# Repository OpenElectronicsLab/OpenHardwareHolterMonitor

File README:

OpenHardwareHolterMonitor is still in early development

This is not a medical device; it is not intended for diagnosis or treatment
of any medical condition.

http://openelectronicslab.github.io/OpenHardwareHolterMonitor/

LICENSE

Software and firmware is licensed under the GPL version 3 as published by the Free Software Foundataion or (at your option) any later version.

https://www.gnu.org/licenses/gpl-3.0.txt

Hardware designs and documentation are licnesed under the CERN Open Hardware
License version 1.1 or (at your option) any later version.

https://www.ohwr.org/licenses/cern-ohl/license_versions/v1.1

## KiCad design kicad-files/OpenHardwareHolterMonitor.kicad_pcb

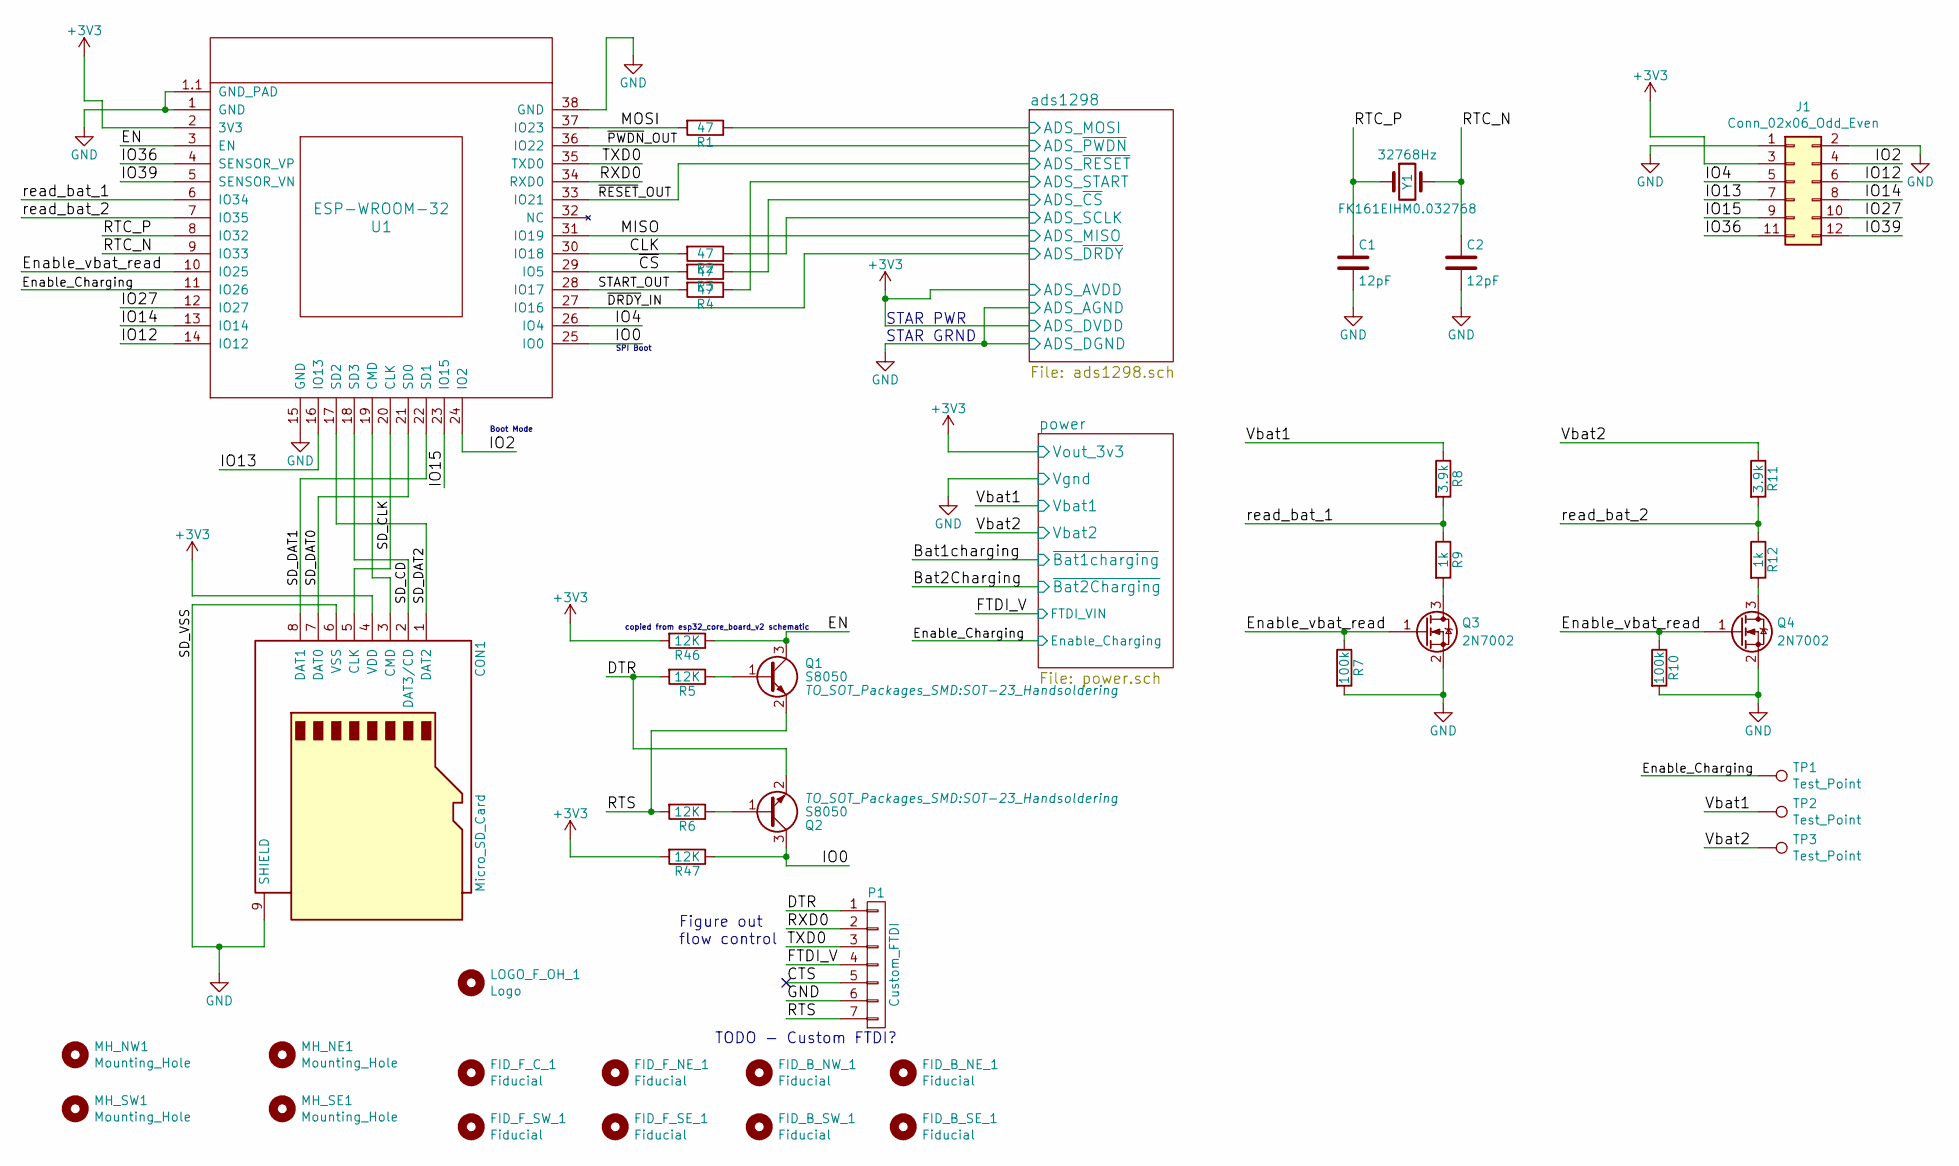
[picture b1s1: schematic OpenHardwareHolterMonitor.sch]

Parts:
C1, C2: 12pF; C_0603_HandSoldering
CON1: Micro_SD_Card; MicroSd_Wurth_693072010801
FID_B_NE_1: Fiducial; Fiducial_1mm_Dia_2.54mm_Outer_CopperTop
FID_B_NW_1: Fiducial; Fiducial_1mm_Dia_2.54mm_Outer_CopperTop
FID_B_SE_1: Fiducial; Fiducial_1mm_Dia_2.54mm_Outer_CopperTop
FID_B_SW_1: Fiducial; Fiducial_1mm_Dia_2.54mm_Outer_CopperTop
FID_F_C_1: Fiducial; Fiducial_1mm_Dia_2.54mm_Outer_CopperTop
FID_F_NE_1: Fiducial; Fiducial_1mm_Dia_2.54mm_Outer_CopperTop
FID_F_SE_1: Fiducial; Fiducial_1mm_Dia_2.54mm_Outer_CopperTop
FID_F_SW_1: Fiducial; Fiducial_1mm_Dia_2.54mm_Outer_CopperTop
J1: Conn_02x06_Odd_Even; Pin_Header_Straight_2x06_Pitch1.27mm
LOGO_F_OH_1: Logo; OSHW-Logo2_9.8x8mm_SilkScreen
MH_NE1: Mounting_Hole; MountingHole_2.2mm_M2_ISO7380
MH_NW1: Mounting_Hole; MountingHole_2.2mm_M2_ISO7380
MH_SE1: Mounting_Hole; MountingHole_2.2mm_M2_ISO7380
MH_SW1: Mounting_Hole; MountingHole_2.2mm_M2_ISO7380
P1: Custom_FTDI; Pin_Header_Straight_1x07_Pitch2.54mm
Q1, Q2: S8050; SOT-23_Handsoldering
Q3, Q4: 2N7002; SOT-23_Handsoldering
R1, R2, R3, R4: 47; R_0603_1608Metric_Pad1.05x0.95mm_HandSolder
R5, R6, R46, R47: 12K; R_0603_1608Metric_Pad1.05x0.95mm_HandSolder
R7, R10: 100k; R_0603_1608Metric_Pad1.05x0.95mm_HandSolder
R8, R11: 3.9k; R_0603_1608Metric_Pad1.05x0.95mm_HandSolder
R9, R12: 1k; R_0603_1608Metric_Pad1.05x0.95mm_HandSolder
TP1, TP2, TP3: Test_Point; Measurement_Point_Square-SMD-Pad_Small
U1: ESP-WROOM-32; MODULE_ESP-WROOM-32
Y1: 32768Hz; K161

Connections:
+3V3: CON1.4 (VDD), J1.3, R46.2, R47.2, U1.2 (3V3); also elsewhere on the board
/CLK: R2.2, U1.30 (IO18)
/CTS: P1.5
/DTR: P1.1, Q2.2 (E), R5.2
/EN: Q1.3 (C), R46.1, U1.3 (EN)
/Enable_Charging: TP1.1, U1.11 (IO26); also elsewhere on the board
/Enable_vbat_read: Q3.1 (G), Q4.1 (G), R7.1, R10.1, U1.10 (IO25)
/FTDI_V: P1.4; also elsewhere on the board
/IO0: Q2.3 (C), R47.1, U1.25 (IO0)
/IO2: J1.4, U1.24 (IO2)
/IO4: J1.5, U1.26 (IO4)
/IO12: J1.6, U1.14 (IO12)
/IO13: J1.7, U1.16 (IO13)
/IO14: J1.8, U1.13 (IO14)
/IO15: J1.9, U1.23 (IO15)
/IO27: J1.10, U1.12 (IO27)
/IO36: J1.11, U1.4 (SENSOR_VP)
/IO39: J1.12, U1.5 (SENSOR_VN)
/MISO: U1.31 (IO19); also elsewhere on the board
/MOSI: R1.2, U1.37 (IO23)
/RTC_N: C2.1, U1.9 (IO33), Y1.2
/RTC_P: C1.1, U1.8 (IO32), Y1.1
/RTS: P1.7, Q1.2 (E), R6.2
/RXD0: P1.2, U1.34 (RXD0)
/SD_CD: CON1.2 (DAT3/CD), U1.18 (SD3)
/SD_CLK: CON1.5 (CLK), U1.20 (CLK)
/SD_DAT0: CON1.7 (DAT0), U1.21 (SD0)
/SD_DAT1: CON1.8 (DAT1), U1.22 (SD1)
/SD_DAT2: CON1.1 (DAT2), U1.17 (SD2)
/START_OUT: R4.2, U1.28 (IO17)
/TXD0: P1.3, U1.35 (TXD0)
/Vbat1: R8.1, TP2.1; also elsewhere on the board
/Vbat2: R11.1, TP3.1; also elsewhere on the board
/ads1298/ADS_MOSI: R1.1; also elsewhere on the board
/ads1298/ADS_SCLK: R2.1; also elsewhere on the board
/ads1298/ADS_START: R4.1; also elsewhere on the board
/ads1298/ADS_~CS~: R3.1; also elsewhere on the board
/read_bat_1: R8.2, R9.1, U1.6 (IO34)
/read_bat_2: R11.2, R12.1, U1.7 (IO35)
/~CS~: R3.2, U1.29 (IO5)
/~DRDY~_IN: U1.27 (IO16); also elsewhere on the board
/~PWDN~_OUT: U1.36 (IO22); also elsewhere on the board
/~RESET~_OUT: U1.33 (IO21); also elsewhere on the board
GND: C1.2, C2.2, CON1.6 (VSS), CON1.9 (SHIELD), J1.1, J1.2, P1.6, Q3.2 (S), Q4.2 (S), R7.2, R10.2, U1.1 (GND), U1.1.1 (GND_PAD), U1.15 (GND), U1.38 (GND); also elsewhere on the board
unnamed: CON1.3 (CMD), U1.19 (CMD)
unnamed: Q1.1 (B), R5.1
unnamed: Q2.1 (B), R6.1
unnamed: Q3.3 (D), R9.2
unnamed: Q4.3 (D), R12.2

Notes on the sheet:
copied from esp32_core_board_v2 schematic
Figure out flow control
Boot Mode
SPI Boot
STAR PWR STAR GRND
TODO - Custom FTDI?

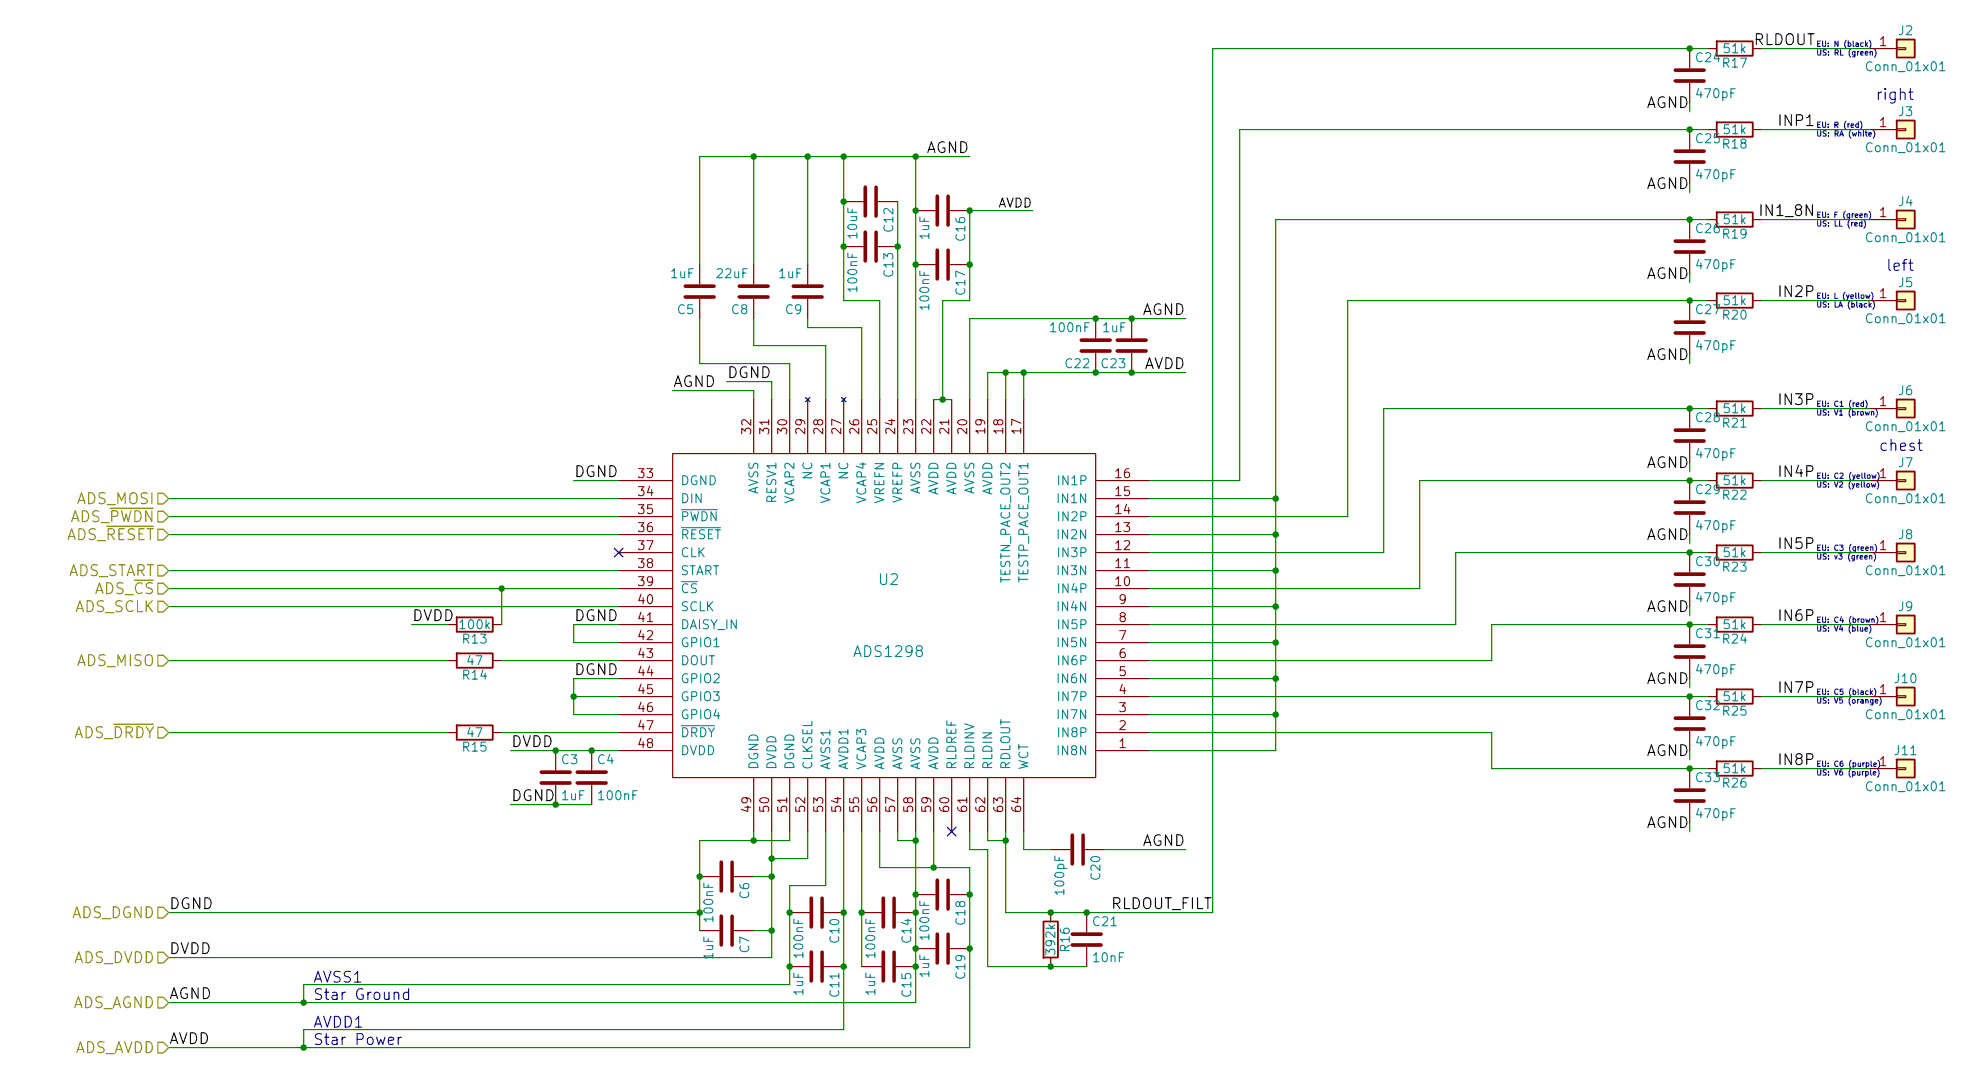
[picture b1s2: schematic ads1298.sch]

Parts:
C3, C5, C7, C9, C11, C15, C16, C19, C23: 1uF; C_0603_HandSoldering
C4, C6, C10, C13, C14, C17, C18, C22: 100nF; C_0603_HandSoldering
C8: 22uF; C_0805_HandSoldering
C12: 10uF; C_0805_HandSoldering
C20: 100pF; C_0603_HandSoldering
C21: 10nF; C_0603_HandSoldering
C24, C25, C26, C27, C28, C29, C30, C31, C32, C33: 470pF; C_0603_HandSoldering
J2, J3, J4, J5, J6, J7, J8, J9, J10, J11: Conn_01x01; PlasticsOne_41828
R13: 100k; R_0603_1608Metric_Pad1.05x0.95mm_HandSolder
R14, R15: 47; R_0603_1608Metric_Pad1.05x0.95mm_HandSolder
R16: 392k; R_0603_1608Metric_Pad1.05x0.95mm_HandSolder
R17, R18, R19, R20, R21, R22, R23, R24, R25, R26: 51k; R_Axial_Power_L20.0mm_W6.4mm_P25.40mm
U2: ADS1298; LQFP-64_10x10mm_Pitch0.5mm

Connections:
+3V3: C3.1, C4.1, C6.1, C7.1, C10.1, C11.1, C16.1, C17.1, C18.1, C19.1, C22.1, C23.1, R13.2, U2.17 (TESTP_PACE_OUT1), U2.18 (TESTN_PACE_OUT2), U2.19 (AVDD), U2.21 (AVDD), U2.22 (AVDD), U2.48 (DVDD), U2.50 (DVDD), U2.52 (CLKSEL), U2.54 (AVDD1), U2.56 (AVDD), U2.59 (AVDD); also elsewhere on the board
/MISO: R14.2; also elsewhere on the board
/ads1298/ADS_MOSI: U2.34 (DIN); also elsewhere on the board
/ads1298/ADS_SCLK: U2.40 (SCLK); also elsewhere on the board
/ads1298/ADS_START: U2.38 (START); also elsewhere on the board
/ads1298/ADS_~CS~: R13.1, U2.39 (~CS~); also elsewhere on the board
/ads1298/IN1_8N: J4.1, R19.1
/ads1298/IN2P: J5.1, R20.1
/ads1298/IN3P: J6.1, R21.1
/ads1298/IN4P: J7.1, R22.1
/ads1298/IN5P: J8.1, R23.1
/ads1298/IN6P: J9.1, R24.1
/ads1298/IN7P: J10.1, R25.1
/ads1298/IN8P: J11.1, R26.1
/ads1298/INP1: J3.1, R18.1
/ads1298/RLDOUT: J2.1, R17.1
/ads1298/RLDOUT_FILT: C21.1, C24.1, R16.1, R17.2, U2.62 (RLDIN), U2.63 (RDLOUT)
/~DRDY~_IN: R15.2; also elsewhere on the board
/~PWDN~_OUT: U2.35 (~PWDN~); also elsewhere on the board
/~RESET~_OUT: U2.36 (~RESET~); also elsewhere on the board
GND: C3.2, C4.2, C5.2, C6.2, C7.2, C8.2, C9.2, C10.2, C11.2, C12.2, C13.2, C14.1, C15.1, C16.2, C17.2, C18.2, C19.2, C20.1, C22.2, C23.2, C24.2, C25.2, C26.2, C27.2, C28.2, C29.2, C30.2, C31.2, C32.2, C33.2, U2.20 (AVSS), U2.23 (AVSS), U2.25 (VREFN), U2.31 (RESV1), U2.32 (AVSS), U2.33 (DGND), U2.41 (DAISY_IN), U2.42 (GPIO1), U2.44 (GPIO2), U2.45 (GPIO3), U2.46 (GPIO4), U2.49 (DGND), U2.51 (DGND), U2.53 (AVSS1), U2.57 (AVSS), U2.58 (AVSS); also elsewhere on the board
unnamed: C5.1, U2.30 (VCAP2)
unnamed: C8.1, U2.28 (VCAP1)
unnamed: C9.1, U2.26 (VCAP4)
unnamed: C12.1, C13.1, U2.24 (VREFP)
unnamed: C14.2, C15.2, U2.55 (VCAP3)
unnamed: C20.2, U2.64 (WCT)
unnamed: C21.2, R16.2, U2.61 (RLDINV)
unnamed: C25.1, R18.2, U2.16 (IN1P)
unnamed: C26.1, R19.2, U2.1 (IN8N), U2.3 (IN7N), U2.5 (IN6N), U2.7 (IN5N), U2.9 (IN4N), U2.11 (IN3N), U2.13 (IN2N), U2.15 (IN1N)
unnamed: C27.1, R20.2, U2.14 (IN2P)
unnamed: C28.1, R21.2, U2.12 (IN3P)
unnamed: C29.1, R22.2, U2.10 (IN4P)
unnamed: C30.1, R23.2, U2.8 (IN5P)
unnamed: C31.1, R24.2, U2.6 (IN6P)
unnamed: C32.1, R25.2, U2.4 (IN7P)
unnamed: C33.1, R26.2, U2.2 (IN8P)
unnamed: R14.1, U2.43 (DOUT)
unnamed: R15.1, U2.47 (~DRDY~)

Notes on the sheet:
AVSS1 Star Ground
AVDD1 Star Power
EU: R (red) US: RA (white)
EU: N (black) US: RL (green)
EU: F (green) US: LL (red)
EU: L (yellow) US: LA (black)
EU: C1 (red) US: V1 (brown)
EU: C2 (yellow) US: V2 (yellow)
EU: C3 (green) US: v3 (green)
EU: C4 (brown) US: V4 (blue)
EU: C5 (black) US: V5 (orange)
EU: C6 (purple) US: V6 (purple)
right
left
chest

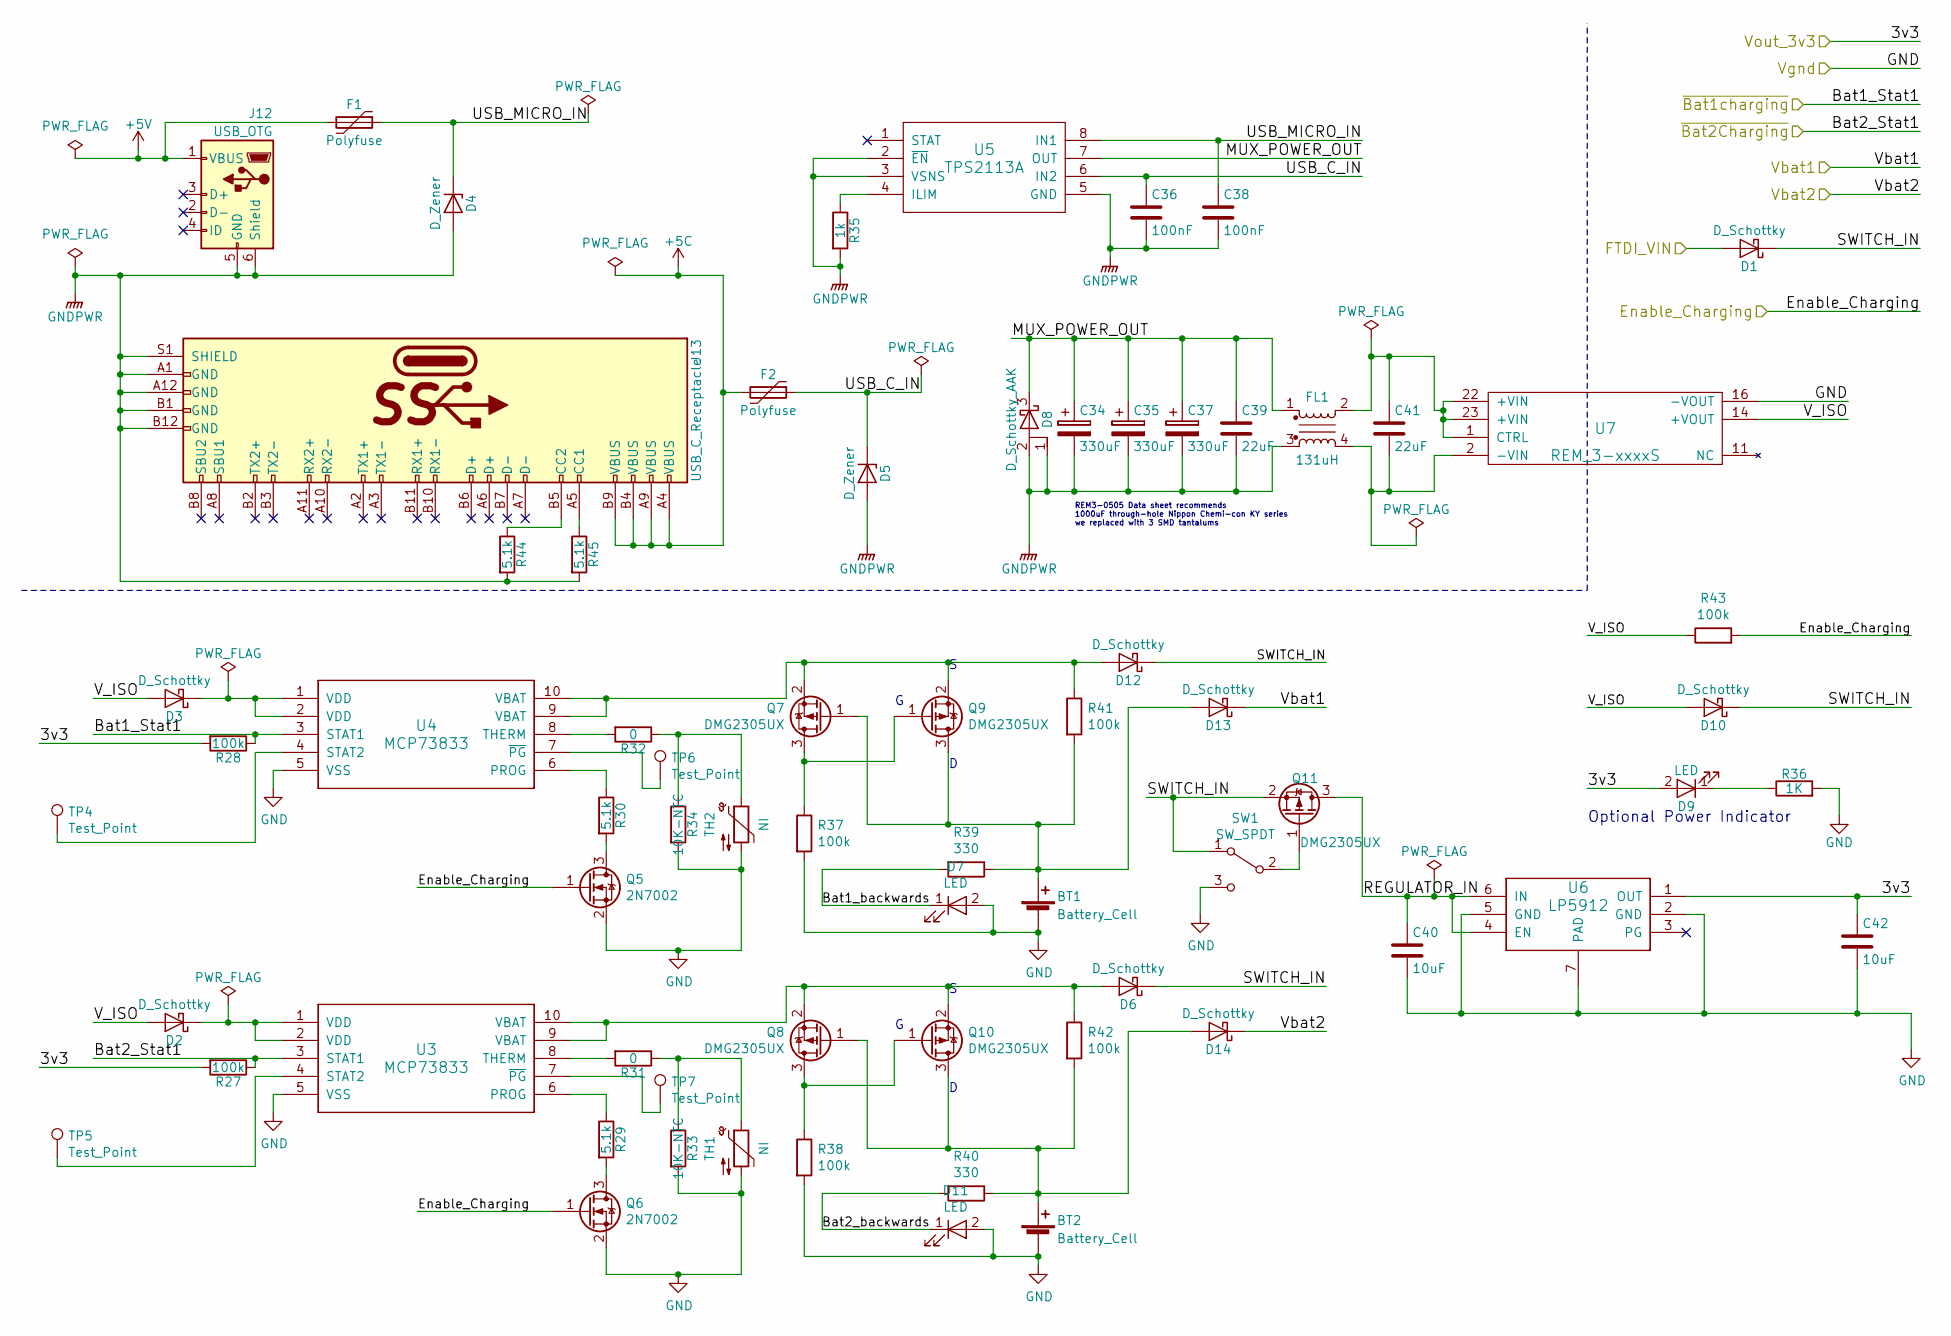
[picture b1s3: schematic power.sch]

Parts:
BT1, BT2: Battery_Cell; Keystone1043
C34, C35, C37: 330uF; CP_Tantalum_Case-E_EIA-7260-38_Hand
C36, C38: 100nF; C_0603_HandSoldering
C39, C41: 22uF; C_0805_HandSoldering
C40, C42: 10uF; C_0805_HandSoldering
D1, D2, D3, D6, D10, D12, D13, D14: D_Schottky; D_SOD-323_HandSoldering
D4, D5: D_Zener; D_SMB_Handsoldering
D7, D9, D11: LED; LED_0603_HandSoldering
D8: D_Schottky_AAK; TO-277A
F1, F2: Polyfuse; R_1812_HandSoldering
FL1: 131uH; CMS1
J12: USB_OTG; USB_Micro-B_Wuerth-629105150521_CircularHoles
J13: USB_C_Receptacle; USB_C_Receptacle_Amphenol_12401610E4-2A_CircularHoles
Q5, Q6: 2N7002; SOT-23_Handsoldering
Q7, Q8, Q9, Q10, Q11: DMG2305UX; SOT-23_Handsoldering
R27, R28, R37, R38, R41, R42, R43: 100k; R_0603_1608Metric_Pad1.05x0.95mm_HandSolder
R29, R30, R44, R45: 5.1k; R_0603_1608Metric_Pad1.05x0.95mm_HandSolder
R31, R32: 0; R_0603_1608Metric_Pad1.05x0.95mm_HandSolder
R33, R34: 10K-NTC; R_0603_1608Metric_Pad1.05x0.95mm_HandSolder
R35: 1k; R_0603_1608Metric_Pad1.05x0.95mm_HandSolder
R36: 1K; R_0603_1608Metric_Pad1.05x0.95mm_HandSolder
R39, R40: 330; R_0603_1608Metric_Pad1.05x0.95mm_HandSolder
SW1: SW_SPDT; SW_SPDT_CK-JS102011SAQN
TH1, TH2: NI; CP_Radial_D4.0mm_P1.50mm
TP4, TP5, TP6, TP7: Test_Point; Measurement_Point_Square-SMD-Pad_Small
U3, U4: MCP73833; MSOP-10_3x3mm_Pitch0.5mm
U5: TPS2113A; TSSOP-8_4.4x3mm_Pitch0.65mm
U6: LP5912; WSON-6_2x2mm_Pitch0.65mm
U7: REM_3-xxxxS; REM3

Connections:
+3V3: C42.1, D9.2 (A), R27.2, R28.2, U6.1 (OUT); also elsewhere on the board
+5C: F2.2, J13.A4 (VBUS), J13.A9 (VBUS), J13.B4 (VBUS), J13.B9 (VBUS)
+5V: F1.2, J12.1 (VBUS)
/Bat1charging: R28.1, U4.3 (STAT1)
/Bat2Charging: R27.1, U3.3 (STAT1)
/Enable_Charging: Q5.1 (G), Q6.1 (G), R43.2; also elsewhere on the board
/FTDI_V: D1.2 (A); also elsewhere on the board
/Vbat1: D13.1 (K); also elsewhere on the board
/Vbat2: D14.1 (K); also elsewhere on the board
/power/Bat1_backwards: D7.1 (K), R39.2
/power/Bat2_backwards: D11.1 (K), R40.2
/power/MUX_POWER_OUT: C34.1, C35.1, C37.1, C39.1, D8.3 (K), FL1.1, U5.7 (OUT)
/power/REGULATOR_IN: C40.1, Q11.3 (D), U6.4 (EN), U6.6 (IN)
/power/SWITCH_IN: D1.1 (K), D6.1 (K), D10.1 (K), D12.1 (K), Q11.2 (S), SW1.1 (A)
/power/USB_C_IN: C36.1, D5.1 (K), F2.1, U5.6 (IN2)
/power/USB_MICRO_IN: C38.1, D4.1 (K), F1.1, U5.8 (IN1)
/power/V_ISO: D2.2 (A), D3.2 (A), D10.2 (A), R43.1, U7.14 (+VOUT)
GND: BT1.2 (-), BT2.2 (-), C40.2, C42.2, D7.2 (A), D11.2 (A), Q5.2 (S), Q6.2 (S), R33.2, R34.2, R36.2, R37.2, R38.2, SW1.3 (C), TH1.2, TH2.2, U3.5 (VSS), U4.5 (VSS), U6.2 (GND), U6.5 (GND), U6.7 (PAD), U7.16 (-VOUT); also elsewhere on the board
GNDPWR: C34.2, C35.2, C36.2, C37.2, C38.2, C39.2, D4.2 (A), D5.2 (A), D8.1 (A), D8.2 (A), FL1.3, J12.5 (GND), J12.6 (Shield), J13.A1 (GND), J13.A12 (GND), J13.B1 (GND), J13.B12 (GND), J13.S1 (SHIELD), R35.2, R44.2, R45.2, U5.2 (~EN~), U5.3 (VSNS), U5.5 (GND)
unnamed: BT1.1 (+), D13.2 (A), Q7.1 (G), Q9.3 (D), R39.1, R41.2
unnamed: BT2.1 (+), D14.2 (A), Q8.1 (G), Q10.3 (D), R40.1, R42.2
unnamed: C41.1, FL1.2, U7.1 (CTRL), U7.22 (+VIN), U7.23 (+VIN)
unnamed: C41.2, FL1.4, U7.2 (-VIN)
unnamed: D2.1 (K), U3.1 (VDD), U3.2 (VDD)
unnamed: D3.1 (K), U4.1 (VDD), U4.2 (VDD)
unnamed: D6.2 (A), Q8.2 (S), Q10.2 (S), R42.1, U3.9 (VBAT), U3.10 (VBAT)
unnamed: D9.1 (K), R36.1
unnamed: D12.2 (A), Q7.2 (S), Q9.2 (S), R41.1, U4.9 (VBAT), U4.10 (VBAT)
unnamed: J13.A5 (CC1), R45.1
unnamed: J13.B5 (CC2), R44.1
unnamed: Q5.3 (D), R30.2
unnamed: Q6.3 (D), R29.2
unnamed: Q7.3 (D), Q9.1 (G), R37.1
unnamed: Q8.3 (D), Q10.1 (G), R38.1
unnamed: Q11.1 (G), SW1.2 (B)
unnamed: R29.1, U3.6 (PROG)
unnamed: R30.1, U4.6 (PROG)
unnamed: R31.1, R33.1, TH1.1
unnamed: R31.2, U3.8 (THERM)
unnamed: R32.1, R34.1, TH2.1
unnamed: R32.2, U4.8 (THERM)
unnamed: R35.1, U5.4 (ILIM)
unnamed: TP4.1, U4.4 (STAT2)
unnamed: TP5.1, U3.4 (STAT2)
unnamed: TP6.1, U4.7 (~PG~)
unnamed: TP7.1, U3.7 (~PG~)

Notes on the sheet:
REM3-0505 Data sheet recommends 1000uF through-hole Nippon Chemi-con KY series we replaced with 3 SMD tantalums
Optional Power Indicator

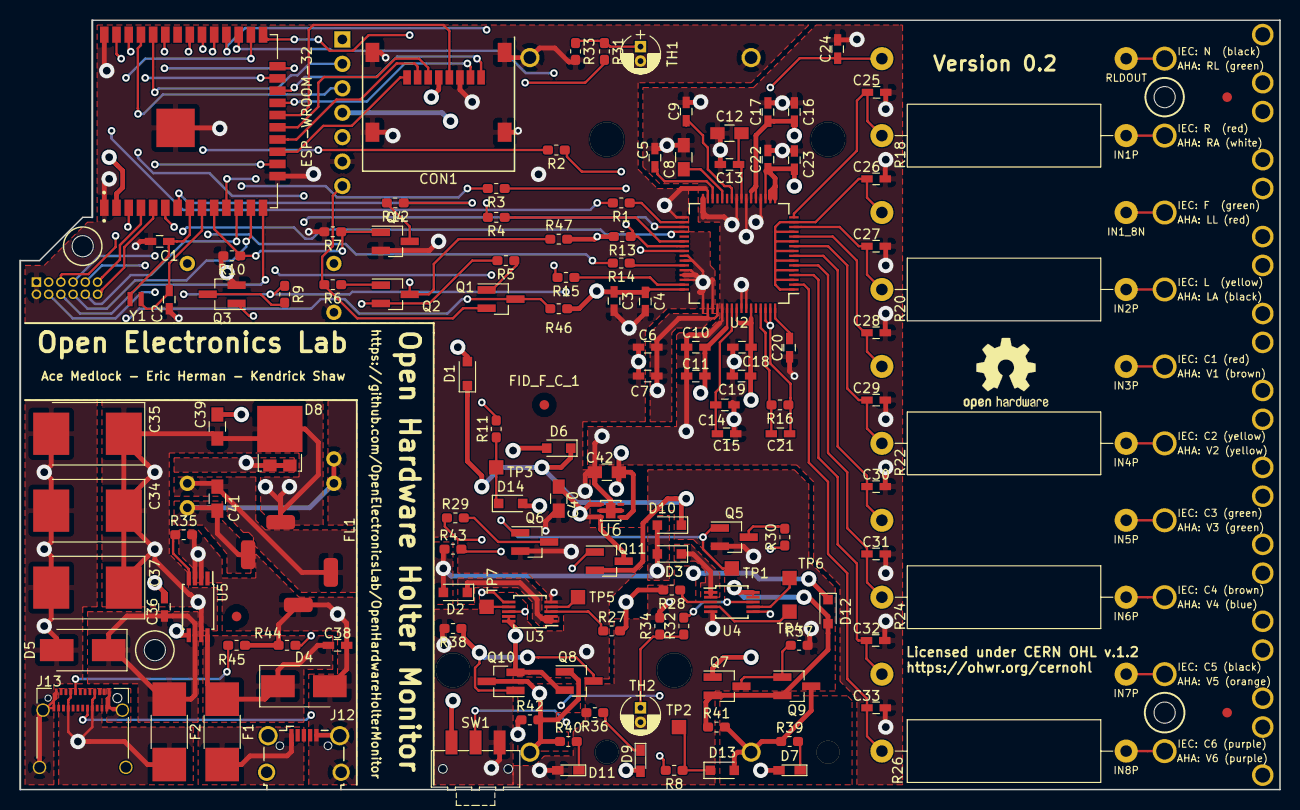
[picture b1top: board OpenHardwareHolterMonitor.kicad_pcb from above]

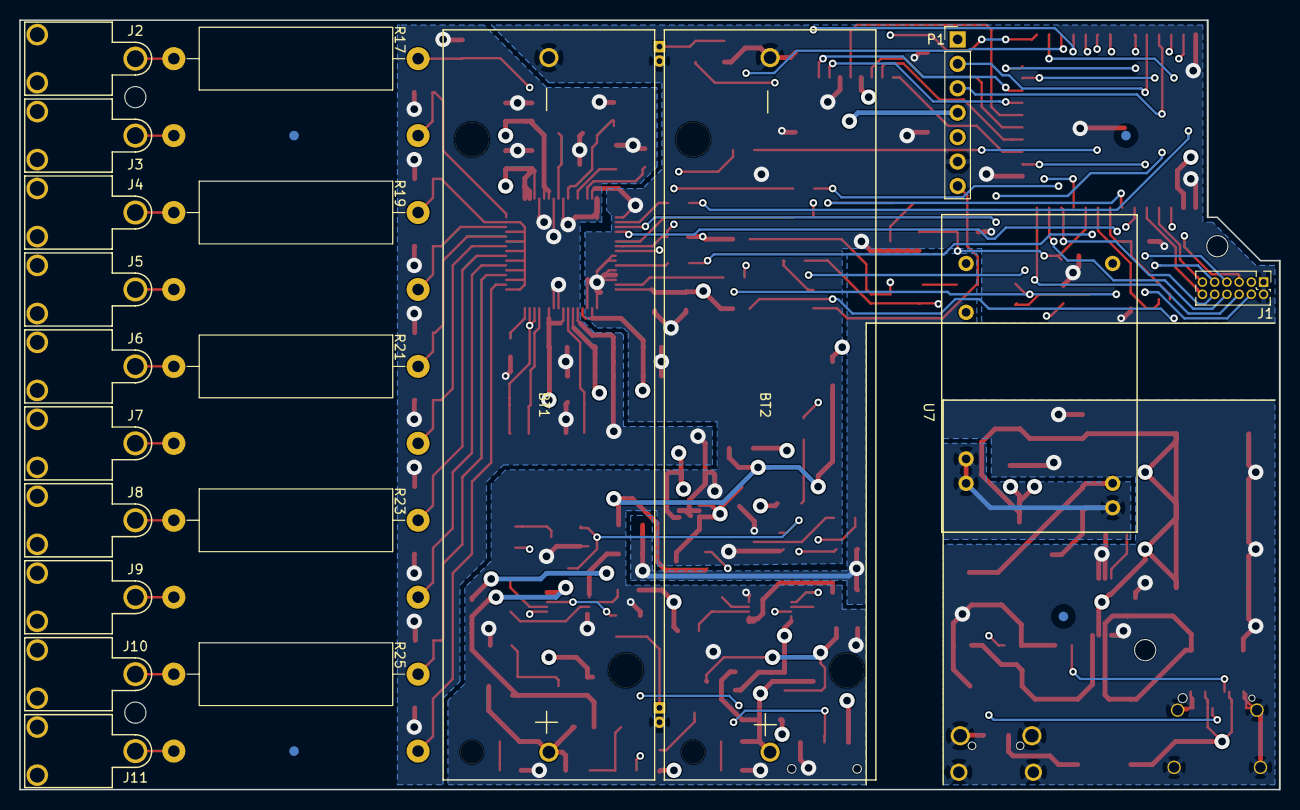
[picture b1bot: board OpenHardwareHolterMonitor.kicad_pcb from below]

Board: 6 copper layers, 131.0 x 80.0 mm, 165 parts (24 on the bottom side), 117 nets.

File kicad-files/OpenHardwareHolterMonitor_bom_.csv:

Component,Description,Part,References,Value,Footprint,Quantity Per PCB,Datasheet,ManufacturerName,manufacturer-pn
1,,Battery_Cell,BT1 BT2,Battery_Cell,Keystone1043,2,,Keystone,1043
2,,C,C4 C6 C10 C13 C14 C17 C18 C22 C36 C38,100nF,C_0603_HandSoldering,10,,Yageo,CC0603JRX7R9BB104
3,,C,C20,100pF,C_0603_HandSoldering,1,,Yageo,CC0603JRNPO9BN101
4,,C,C21,10nF,C_0603_HandSoldering,1,,Samsung Electro-Mechanics,CL10B103KB8NCNC
5,,C,C12 C40 C42,10uF,C_0805_HandSoldering,3,,Samsung Electro-Mechanics,CL21B106KPQNNNE
6,,C,C1 C2,12pF,C_0603_HandSoldering,2,,Yageo,CC0603JRNPO9BN120
7,,C,C3 C5 C7 C9 C11 C15 C16 C19 C23,1uF,C_0603_HandSoldering,9,,Taiyo Yuden,LMK107B7105KA-T
8,,C,C8 C39 C41,22uF,C_0805_HandSoldering,3,,Murata Electronics,GRM21BD71A226ME44L
9,,CP,C34 C35 C37,330uF,CP_Tantalum_Case-E_EIA-7260-38_Hand,3,,AVX,TPSE337K010T0050V
10,,C,C24 C25 C26 C27 C28 C29 C30 C31 C32 C33,470pF,C_0603_HandSoldering,10,,Yageo,CC0603JRNPOYBN471
11,,Micro_SD_Card,CON1,Micro_SD_Card,MicroSd_Wurth_693072010801,1,,Wurth,693072010801
12,,D_Schottky,D1 D2 D3 D6 D10 D12 D13 D14,D_Schottky,D_SOD-323_HandSoldering,8,,STMicroelectronics,BAT60JFILM
13,,D_Schottky_AAK,D8,D_Schottky_AAK,TO-277A,1,,Vishay,SS10PH10-M3/86A
14,,D_Zener,D4 D5,D_Zener,D_SMB_Handsoldering,2,,Micro Commercial Components (MCC),SMBJ5339B-TP
15,,LED-device,D7 D11,LED,LED_0603_HandSoldering,2,~,Inolux,IN-S63BTA
16,,LED,D9,LED,LED_0603_HandSoldering,1,,Lite-On Inc.,LTST-C191KGKT
17,,Polyfuse,F1 F2,Polyfuse,R_1812_HandSoldering,2,,Littelfuse,1812L050/60MR
18,,EMI_Filter_LL,FL1,131uH,CMS1,1,,Eaton,CMS1-12-R
19,,Conn_01x01,J2 J3 J4 J5 J6 J7 J8 J9 J10 J11,Conn_01x01,PlasticsOne_41828,10,,PlasticsOne,41828
20,,Conn_02x06_Odd_Even-Connector,J1,Conn_02x06_Odd_Even,Pin_Header_Straight_2x06_Pitch1.27mm,1,~,Harwin,M50-3000645
21,,USB_C_Receptacle,J13,USB_C_Receptacle,USB_C_Receptacle_Amphenol_12401610E4-2A_CircularHoles,1,,Amphenol,12401610E4#2A
22,,USB_OTG,J12,USB_OTG,USB_Micro-B_Wuerth-629105150521_CircularHoles,1,,Wurth,629105150521
23,,CONN_01X07,P1,Custom_FTDI,Pin_Header_Straight_1x07_Pitch2.54mm,1,,Wurth,61300711121
24,,Q_NMOS_DGS,Q3 Q4,Q_NMOS_DGS,SOT-23W_Handsoldering,2,,Diodes Incorporated,2N7002-7-F
25,,Q_NMOS_DGS-device,Q5 Q6,Q_NMOS_DGS,SOT-23W_Handsoldering,2,,Diodes Incorporated,2N7002-7-F
26,,Q_PMOS_DGS-device,Q7 Q8 Q9 Q10 Q11,Q_PMOS_DGS,SOT-23_Handsoldering,5,,Diodes Incorporated,DMG2305UX
27,,S8050,Q1 Q2,S8050,SOT-23_Handsoldering,2,,Diodes Incorporated,DSS4240T-7
28,,R,R31 R32,0,R_0603_HandSoldering,2,,Yageo,RC0603FR-070RL
29,,R,R7 R10 R13 R27 R28,100k,R_0603_HandSoldering,5,,Panasonic Electronic Components,ERA-3AEB104V
30,,R-device,R37 R38 R41 R42 R43,100k,R_0603_HandSoldering,5,,Panasonic Electronic Components,ERA-3AEB104V
31,,R,R33 R34,10K-NTC,R_0603_HandSoldering,2,,Panasonic Electronic Components,ERT-J1VG103JA
32,,R,R5 R6,12K,R_0603_HandSoldering,2,,Panasonic Electronic Components,ERJ-PB3B1202V
33,,R,R9 R12 R35 R36,1k,R_0603_HandSoldering,4,,Panasonic Electronic Components,ERJ-PB3B1001V
34,,R,R8 R11,3.9k,R_0603_HandSoldering,2,,Panasonic Electronic Components,ERJ-PB3B3901V
35,,R-device,R39 R40,330,R_0603_HandSoldering,2,,Panasonic Electronic Components,ERA-3AEB331V
36,,R,R16,392k,R_0603_HandSoldering,1,,TE Connectivity Passive Product,RN73C1J392KBTD
37,,R,R1 R2 R3 R4 R14 R15,47,R_0603_HandSoldering,6,,Panasonic Electronic Components,ERA-3AEB470V
38,,R,R29 R30,5.1k,R_0603_HandSoldering,2,,Panasonic Electronic Components,ERJ-PB3B5101V
39,,R,R17 R18 R19 R20 R21 R22 R23 R24 R25 R26,51k,R_Axial_Power_L20.0mm_W6.4mm_P25.40mm,10,,Stackpole Electronics,ASRM2JA51K0
40,"Switch, single pole double throw",SW_SPDT,SW1,SW_SPDT,SW_SPDT_CK-JS102011SAQN,1,,C&K,JS102011SAQN
41,,Thermistor_NTC,TH1 TH2,NI,CP_Radial_D4.0mm_P1.50mm,2,,,
42,,ADS1298,U2,ADS1298,LQFP-64_10x10mm_Pitch0.5mm,1,,Texas Instruments,ADS1298IPAG
43,,ESP-WROOM-32,U1,ESP-WROOM-32,MODULE_ESP-WROOM-32,1,,RF Solutions,ESP-32
44,,LP5912,U6,LP5912,WSON-6_2x2mm_Pitch0.65mm,1,,Texas Instruments,LP5912-3.3DRVT
45,,MCP73833,U3 U4,MCP73833,MSOP-10_3x3mm_Pitch0.5mm,2,,Microchip Technology,MCP73833T-AMI/UN
46,,REM_3-xxxxS,U7,REM_3-xxxxS,REM3,1,,Recom Power,REM3-0505S/A
47,,TPS2113A,U5,TPS2113A,TSSOP-8_4.4x3mm_Pitch0.65mm,1,,Texas Instruments,TPS2113A
48,,Crystal,Y1,32768Hz,K161,1,,Fox,FK161EIHM0.032768





Component Groups:,48
Component Count:,141
Fitted Components:,141
Number of PCBs:,1
Total components:,141
Schematic Version:,
Schematic Date:,
BoM Date:,Sat 09 Mar 2019 03:22:51 PM CET
Schematic Source:,/home/eric/src/OpenHardwareHolterMonitor/kicad-files/OpenHardwareHolterMonitor.sch
KiCad Version:,Eeschema 5.0.2+dfsg1-1

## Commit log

2017-12-02 init
2017-12-02 GPLv3+
2017-12-02 README
2017-12-02 CERN OHL v1.1
2017-12-02 GPLv3+, CERN OHLv1.1+
2017-12-02 gitignore
2017-12-02 ESP32 for kicad
    data sheet at:
    https://cdn.sparkfun.com/datasheets/IoT/esp32_datasheet_en.pdf
2017-12-02 checkpoint schematic with ESP32
2017-12-02 ESP32 add ground pad as pin 49
    version 2 of the datasheet:
    https://www.espressif.com/sites/default/files/documentation/esp32_datasheet_en.pdf
2017-12-02 ESP-WROOM-32
    http://espressif.com/sites/default/files/documentation/esp-wroom-32_datasheet_en.pdf
2017-12-02 checkpoint
2017-12-09 copy ADS1299 parts from OpenHardwareExG project
2017-12-09 checkpoint with SD card and ADS sketched-in
2017-12-09 sketch in some connections
2017-12-09 add ADS1298 from ads1298-breakout project
2017-12-09 swap-in 1298
2017-12-09 fix lib location
2017-12-25 extract ADS into separate sheet
2017-12-25 add power decoupling caps to ADS
2017-12-25 ads schematic cleanup and add source termination
2018-01-06 add anti-aliasing filters
2018-01-06 some power notes
2018-01-13 power notes
2018-01-13 voltage drop notes
2018-01-27 simplify anti-aliasing filter
    new low-pass filter cuts off at about 6.6KHz
    >>> 1/(2 * math.pi * 51e3 * 470e-12)
    6639.755656733221
2018-01-27 add components LP592 and MCP73833
2018-01-27 sketch-in a battery
2018-02-10 raw math notes on thermister resistor calculations
2018-02-10 sketch-in thermister to power sheet
2018-03-17 fix link
2018-03-17 add a DC-to-DC isolator
2018-03-17 added micro-USB and isolated power
2018-03-24 schematic first draft
2018-03-24 add vbat to header, and optional power LED
2018-04-15 kicad-4.0.7
2018-04-15 sketch-in USB C power option, TODO: add power muxer
2018-06-02 multiplex power-in
2018-06-02 fix rules-check issues
2018-06-02 assign some footprints
2018-06-09 kicad from git repo
    https://git.launchpad.net/kicad
    8444b1b6176249060196c22cf0d5027d92f93854
    https://git.launchpad.net/kicad-library
    bb856328eef2676d859dfa179a6c078922a42274
2018-06-09 add some footprints
2018-06-16 more footprints
2018-06-16 cyrozap: Added module for TI WSON-6 with thermal pad
    https://github.com/cyrozap/KiCad/commit/2442131550df7426408fbe5ab2eadaa1c536b14e
2018-06-16 add OLIMEX footprint for ESP-WROOM-32
    https://www.snapeda.com/parts/ESP-WROOM-32/Olimex%20LTD/view-part/
    https://www.olimex.com/Products/IoT/ESP32-WROOM-32/
2018-06-16 more footprint usage
2018-06-16 finish footprints
2018-06-16 mv WSON into kicad-files
2018-09-15 add note from Med Instr Design & Dev
2018-09-15 checkpoint initial pcb file
2018-09-15 checkpoint 2 pcb file
2018-09-15 checkpoint 3 pcb file
2018-10-13 wire-up power/gnd, caps to ads1298
2018-10-13 add TODO section
2018-10-20 checkpoint; non-isolated layout
2018-10-20 checkpoint layout
2018-10-20 next up, isolated power layout
2018-11-03 add battery reversal protection to schematic
2018-11-03 un-isolated power layout
2018-11-03 board layout checkpoint
2018-11-03 checkpoint PCB
2018-11-10 charger layout
2018-11-24 initial hook-up of isolated side
2018-11-24 non-isolated hook-up
2018-11-24 pre-notch checkpoint
2018-11-24 ready for holes and zones
2018-12-01 checkpoint for kicad upgrade
2018-12-01 switch to 6 layer board
2018-12-01 power lines 0.5mm
2018-12-01 isolated ground planes
2018-12-08 widen power tracks
2018-12-08 finishing up zones
2018-12-15 add testing device idea notes
2018-12-15 DRC passes (with some missing courtyard warnings)
2018-12-15 esp-wroom footprint update
2018-12-15 add basic courtyards to footprints
2018-12-17 add debug labels
2018-12-22 align physical items with schematic
2018-12-22 add the first few part numbers
2019-01-05 add fiducial marks
2019-01-05 Add logos and text to silkscreen layer
2019-01-05 add gerber files
2019-01-12 continue assigning part numbers for BOM
2019-01-19 replace switch and rework pcb
2019-01-19 flipped alternating resistors to increase clearance between
2019-01-19 more parts of the BOM
2019-01-26 fix some part typos
2019-01-26 someone set us up the BoM
2019-02-09 checked BoM
2019-02-09 eliminate old notes from schematic or move to notes.txt
2019-02-09 fix-up pcb with new footprints
2019-03-09 checkpoint silk layout
2019-03-09 finish board v0.1
2019-03-09 generate gerbers
2019-03-09 note minor shortcomings discovered inspecting gerbers
2019-03-09 generated BOM
2019-03-09 add a goldphoenix BoM without touchproof connectors
2019-03-16 rework BoM via digikey for goldphoenix
2019-03-24 current footprints do not have 3d models
2019-06-08 add a TODO: BT1 == BAT2
2019-06-15 note options for board errors
2019-06-22 add diagrams for bad transitor footprints
2019-06-22 fix schematic to use standard transistor pin numbers
2019-06-22 switch to consistent SOT-23 footprint
2019-06-22 fixed pcb for transistor pinouts
2019-07-13 re-add Fiducial marks
2019-07-13 re-add open hardware logo
2019-07-13 Align Fiducials and Logo on schematic and PCB
2019-07-13 refill & DRC
2019-07-13 fix lables R17-R26
2019-07-13 align back copper power zone with other layers
2019-07-13 fix CMS1 footprint
2019-08-17 add note about pcb spacing question
2019-08-24 more things for next rev
2019-08-24 starting on case design
2019-08-31 case: finish board keepout model
2019-08-31 refactoring of case OpenSCAD code
2019-08-31 initial minimal case design
2019-08-31 add case screw holes
2019-09-21 increase clearance based on prototype
2019-09-21 increase tolerances
2019-09-21 slope case bottom
2019-09-21 round the corners
2019-09-21 increase hex counter-sinks
2019-09-21 widen screw holes
2019-09-21 linebreaks on very long lines
2019-09-28 notes on case design from test print
2019-09-28 programmable LED?
2019-10-12 notes from hardware debugging
2019-10-19 label off and on
2019-10-19 expose I0 and EN on FTDI header?
2019-10-26 add pull-up resistors to EN and IO0
2019-10-26 Boston board needs some TLC
2019-11-09 Not a medical device
2019-11-09 add code of conduct file
2021-02-20 update notes

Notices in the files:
kicad-files/OpenHardwareHolterMonitor.kicad_pcb:
Licensed under CERN OHL v.1.2
